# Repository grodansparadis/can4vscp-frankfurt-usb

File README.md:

<h1>Frankfurt USB</h1>

Buffered and isolated interface for CAN4VSCP

Frankurt USB is a high speed USB interface to the CAN4VSCP bus. It is not available inte 
<a href="http://www.frogshop.se">FrogShop</a> at the moment but will probaly be available this year.

It is planed in two versions. One for DIN montage/wall mountage as the rest of the CAN4VSCP modules and
one version that is boxed.
<hr>

This project is part of the <a href="http://www.vscp.org">VSCP (Very Simple Control Protocol) project</a>. 

<hr>

This project is licensed under the 
<a href="http://creativecommons.org/licenses/by-nc-sa/3.0/">Creative Commons open source license Attribution-NonCommercial-ShareAlike 3.0 Unported</a>. 
Other license options are available by conacting <a href="malto:info@grodansparadis.com">Paradis of the Frog AB</a>

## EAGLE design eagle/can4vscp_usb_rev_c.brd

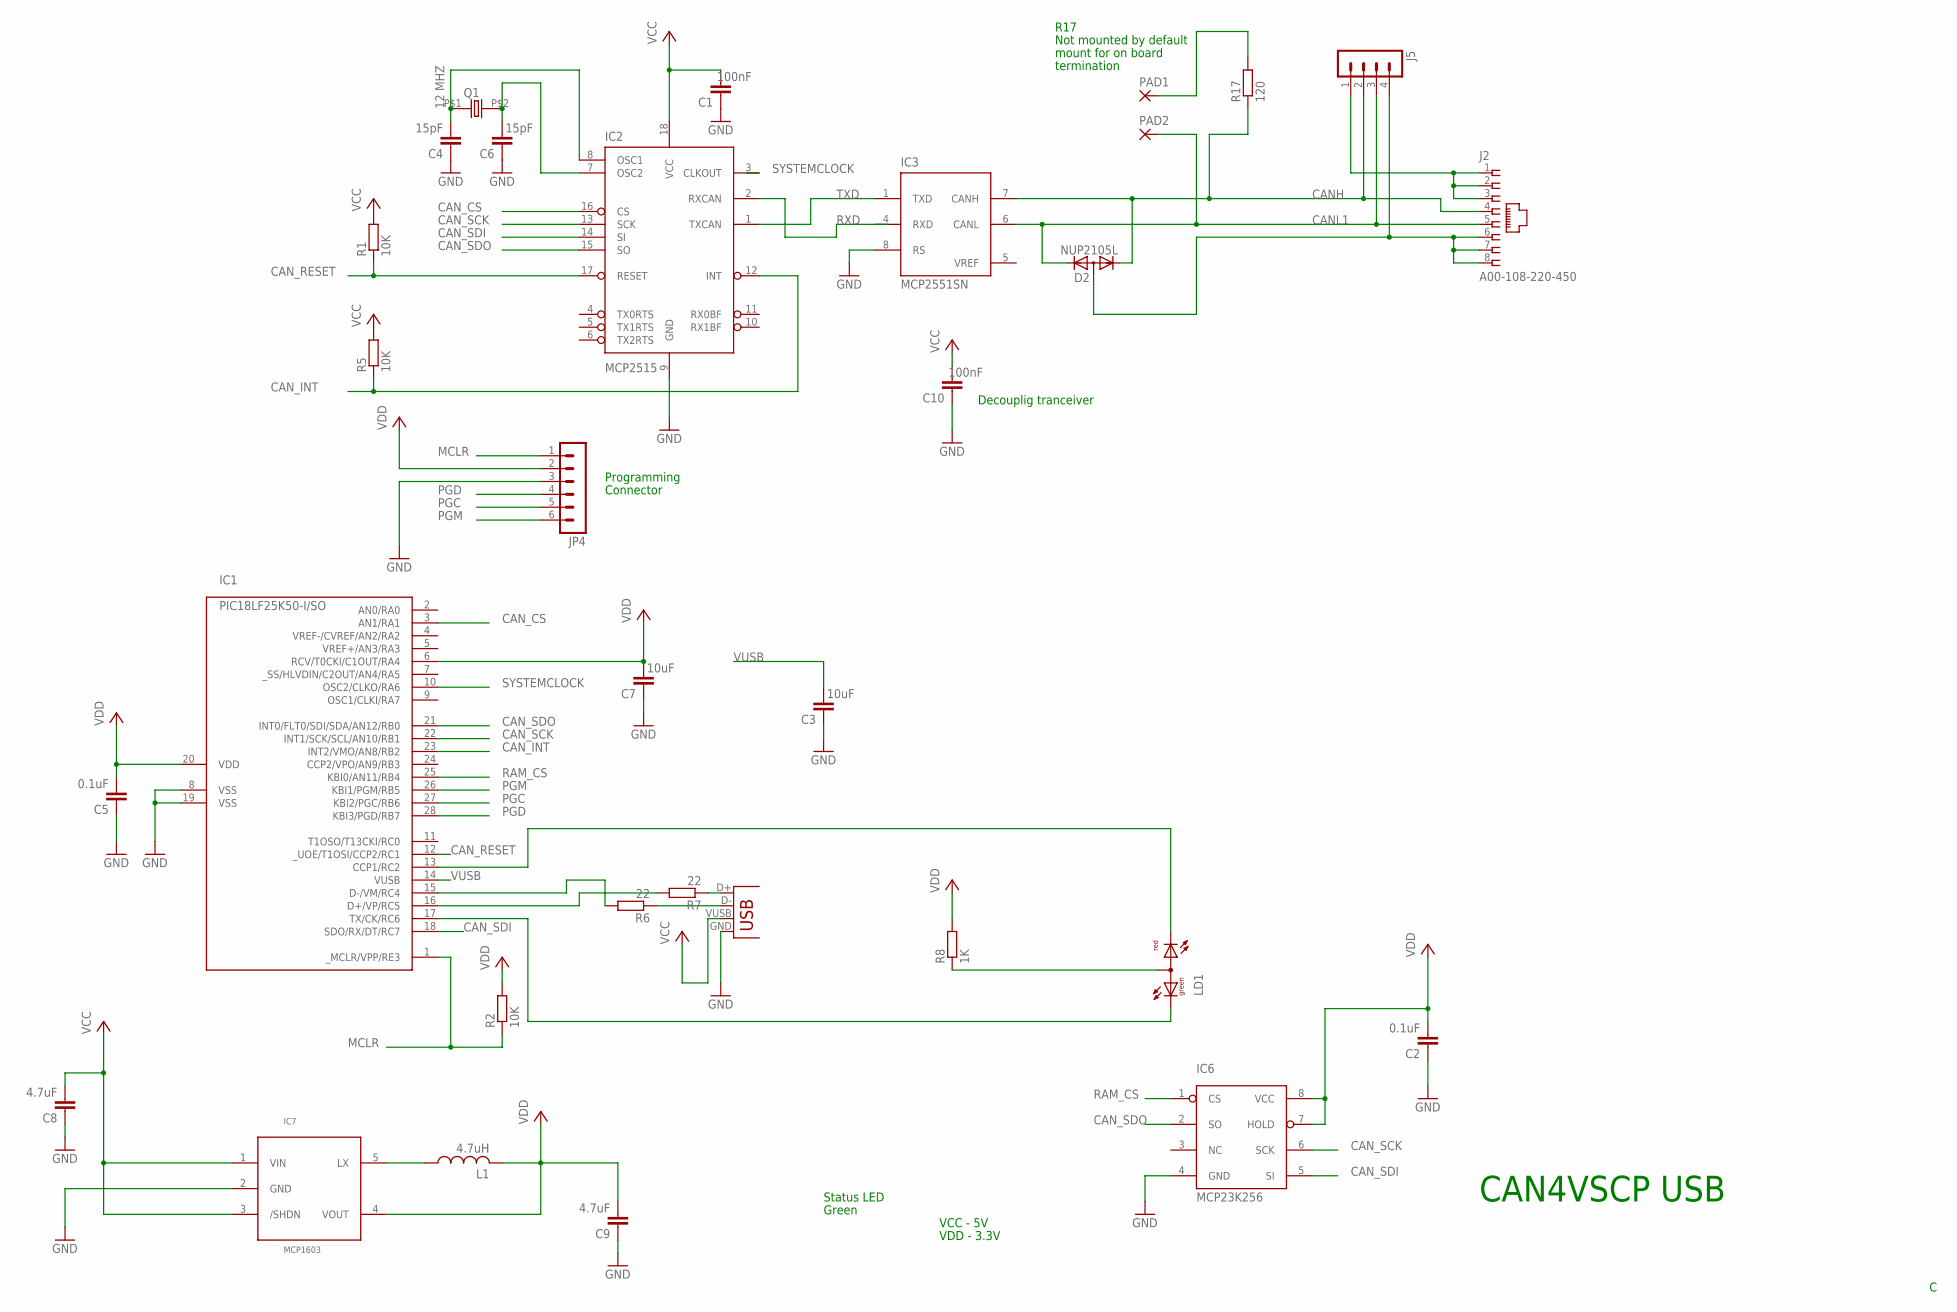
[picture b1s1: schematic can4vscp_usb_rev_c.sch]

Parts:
C1, C10: 100nF; C0805
C2, C5: 0.1uF; C0805
C3, C7: 10uF; C0805
C4, C6: 15pF; C0805
C8, C9: 4.7uF; C0805
D2: NUP2105L; SOT23
IC1: PIC18LF25K50-I/SO; SO-28W
IC2: MCP2515; SO-18W
IC3: MCP2551SN; SO-08
IC6: MCP23K256; SO-8
IC7: MCP1603; SOT23-5L
J2: A00-108-220-450; RJ-45
J4: USB-B-S; USB-B-SMT
J5: MA04-1
JP4: MA06-1
L1: 4.7uH; L2012C
LD1: DUOLED-RG-A; DUOLED-A-5MM
PAD1, PAD2: 1,6/0,8
Q1: 12 MHZ; 9C
R1, R2, R5: 10K; R0805
R6, R7: 22; R0805
R8: 1K; R0805
R17: 120; R0805

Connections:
CANH: D2.1 (K1), IC3.7 (CANH), J2.4, J5.2, R17.1
CANL1: D2.2 (K2), IC3.6 (CANL), J2.5, J5.3, PAD2.1
CAN_CS: IC1.3 (AN1/RA1), IC2.16 (CS)
CAN_INT: IC1.23 (INT2/VMO/AN8/RB2), IC2.12 (INT), R5.1
CAN_RESET: IC1.12 (_UOE/T1OSI/CCP2/RC1), IC2.17 (RESET), R1.1
CAN_SCK: IC1.22 (INT1/SCK/SCL/AN10/RB1), IC2.13 (SCK), IC6.6 (SCK)
CAN_SDI: IC1.18 (SDO/RX/DT/RC7), IC2.14 (SI), IC6.5 (SI)
CAN_SDO: IC1.21 (INT0/FLT0/SDI/SDA/AN12/RB0), IC2.15 (SO), IC6.2 (SO)
GND: C1.1, C2.1, C3.1, C4.1, C5.1, C6.1, C7.1, C8.1, C9.1, C10.1, D2.3 (A), IC1.8 (VSS), IC1.19 (VSS), IC2.9 (GND), IC3.2 (VSS), IC3.8 (RS), IC6.4 (GND), IC7.2 (GND), J2.6, J2.7, J2.8, J4.GND, J5.4, JP4.3
MCLR: IC1.1 (_MCLR/VPP/RE3), JP4.1, R2.1
unnamed: IC1.16 (D+/VP/RC5), R7.2
unnamed: C4.2, IC2.8 (OSC1), Q1.P$1 (1)
unnamed: IC1.15 (D-/VM/RC4), R6.2
unnamed: IC1.13 (CCP1/RC2), LD1.CR
unnamed: C6.2, IC2.7 (OSC2), Q1.P$2 (2)
unnamed: LD1.A, R8.1
unnamed: IC1.17 (TX/CK/RC6), LD1.CX (CG)
unnamed: PAD1.1, R17.2
unnamed: J2.1, J2.2, J2.3, J5.1
unnamed: J4.D-, R6.1
unnamed: J4.D+, R7.1
unnamed: IC7.5 (LX), L1.1
PGC: IC1.27 (KBI2/PGC/RB6), JP4.5
PGD: IC1.28 (KBI3/PGD/RB7), JP4.4
PGM: IC1.26 (KBI1/PGM/RB5), JP4.6
RAM_CS: IC1.25 (KBI0/AN11/RB4), IC6.1 (CS)
RXD: IC2.2 (RXCAN)
SYSTEMCLOCK: IC1.10 (OSC2/CLKO/RA6), IC2.3 (CLKOUT)
TXD: IC2.1 (TXCAN), IC3.1 (TXD)
VCC: C1.2, C8.2, C10.2, IC2.18 (VCC), IC3.3 (VDD), IC7.1 (VIN), IC7.3 (/SHDN), J4.VUSB (VBUS), R1.2, R5.2
VDD: C2.2, C5.2, C7.2, C9.2, IC1.6 (RCV/T0CKI/C1OUT/RA4), IC1.20 (VDD), IC6.7 (HOLD), IC6.8 (VCC), IC7.4 (VOUT), JP4.2, L1.2, R2.2, R8.2
VREF: IC3.5 (VREF)
VUSB: C3.2, IC1.14 (VUSB)

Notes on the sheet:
Programming
Connector
CAN4VSCP USB
Status LED
Green
Not mounted by default
mount for on board
termination
R17
VCC - 5V
VDD - 3.3V
Decouplig tranceiver

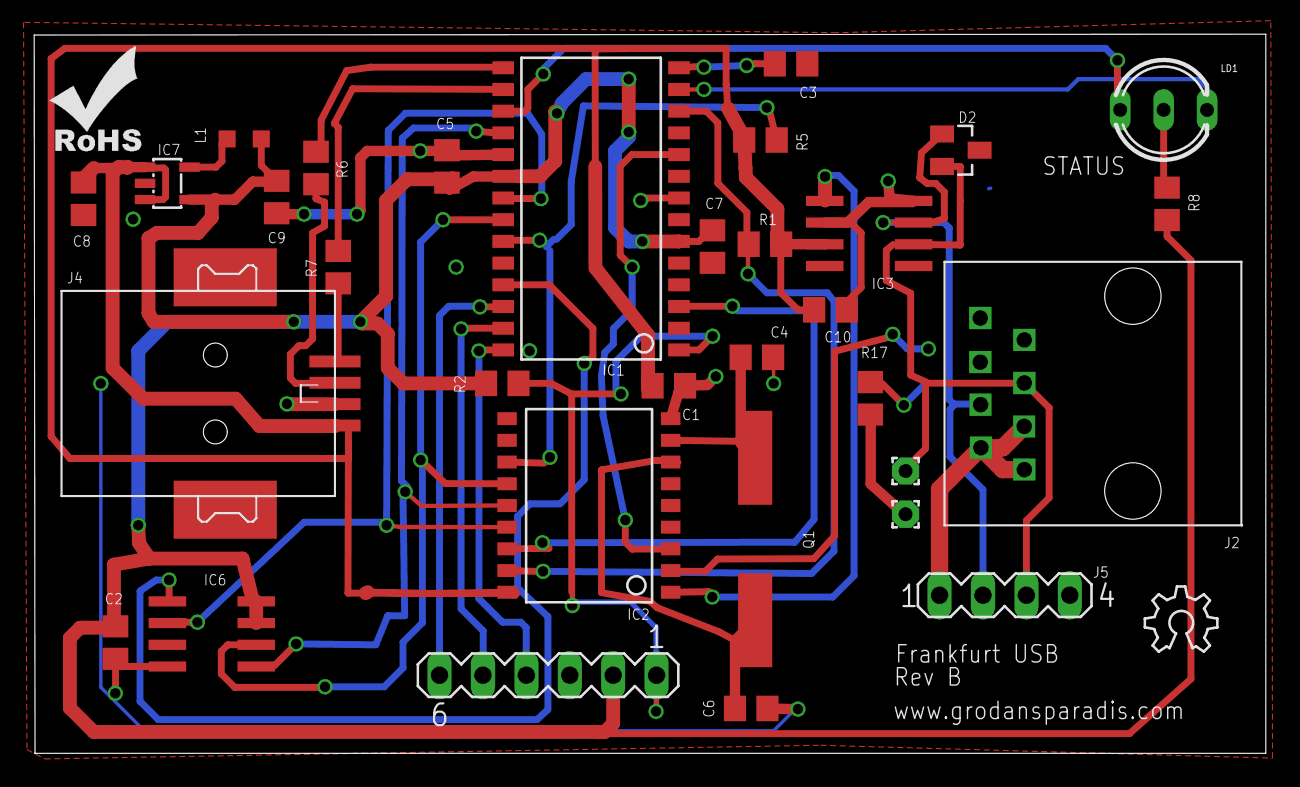
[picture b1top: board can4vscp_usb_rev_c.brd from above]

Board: 2 copper layers, 72.1 x 42.1 mm, 35 parts (0 on the bottom side), 31 nets.

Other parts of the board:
U$1: OSHW_6X150_NOTEXT
U$2: ROHS_SILK
U$4: VSCP_LOGO2

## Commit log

2015-08-17 Initial checkin
2015-08-17 Ignoring work files
2015-08-17 updated initial info
2015-08-17 Changed license to Artistic License 3.0
2015-08-28 Removed junk
2015-11-03 Added boxed version and stepped to rev c
2015-11-03 Adding gerbers for the enclosure version
2015-12-03 Corrected processor type
2015-12-17 Updated readme and license
2023-03-07 rev c
2023-04-11 Removed Patreon as sponsor option
2025-09-30 /home/akhe/development/VSCP/can4vscp-odessa/LICENSE
2026-05-04 Added new STM32 based design
2026-05-04 Removed manual dirt
2026-05-04 Changed crystal to TXC 7V series
2026-05-04 Fixed power issue
2026-05-04 Added butons
2026-05-05 Updated license to CERN
2026-05-08 Reversion A schema and PCB
2026-05-08 Fixed 3D models
